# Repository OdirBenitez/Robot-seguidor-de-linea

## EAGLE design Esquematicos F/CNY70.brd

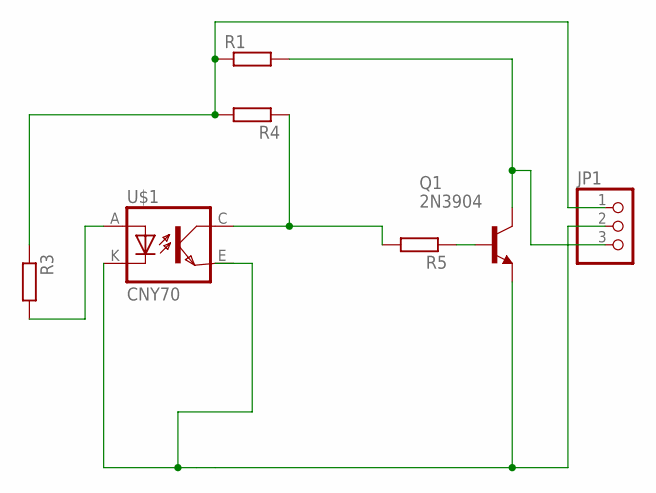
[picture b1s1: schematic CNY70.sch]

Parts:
JP1: PINHD-1X3; 1X03
Q1: 2N3904; TO92
R1, R3, R4, R5: R-EU_0207/10; 0207/10
U$1: CNY70; 4

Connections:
unnamed: Q1.2 (B), R5.1
unnamed: JP1.2, Q1.3 (E)
unnamed: JP1.1, R1.1, R3.1, R4.2
unnamed: U$1.E (EMI), U$1.K (C)
unnamed: JP1.3, Q1.1 (C), R1.2
unnamed: R3.2, U$1.A
unnamed: R4.1, R5.2, U$1.C (COL)

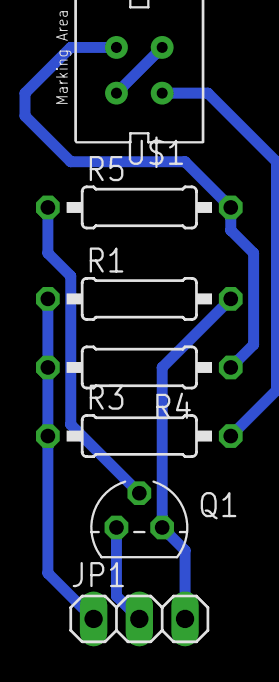
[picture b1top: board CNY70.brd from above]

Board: 2 copper layers, 7 parts (0 on the bottom side), 7 nets.

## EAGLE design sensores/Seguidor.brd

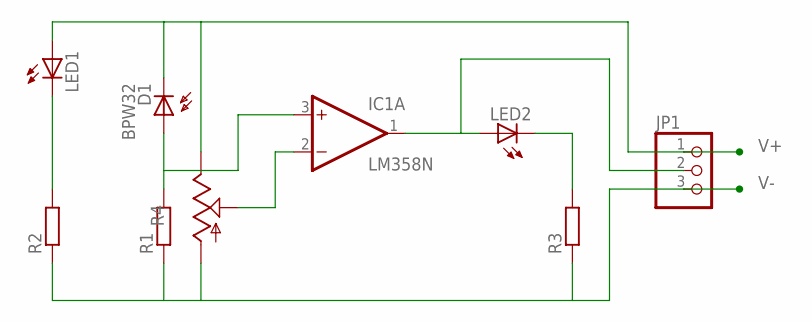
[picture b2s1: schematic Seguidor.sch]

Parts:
D1: BPW32
IC1: LM358N; DIL08
JP1: PINHD-1X3; 1X03
LED1, LED2: LED3MM
R1, R2, R3: R-EU_0207/12; 0207/12
R4: TRIM_US-B25P; B25P

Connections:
unnamed: D1.A, IC1.3 (+IN), R1.2
unnamed: LED1.K (C), R2.2
unnamed: IC1.1 (OUT), JP1.2, LED2.A
unnamed: IC1.2 (-IN), R4.S
unnamed: LED2.K (C), R3.2
V+: D1.K (C), IC1.8 (V+), JP1.1, LED1.A, R4.E
V-: IC1.4 (V-), JP1.3, R1.1, R2.1, R3.1, R4.A

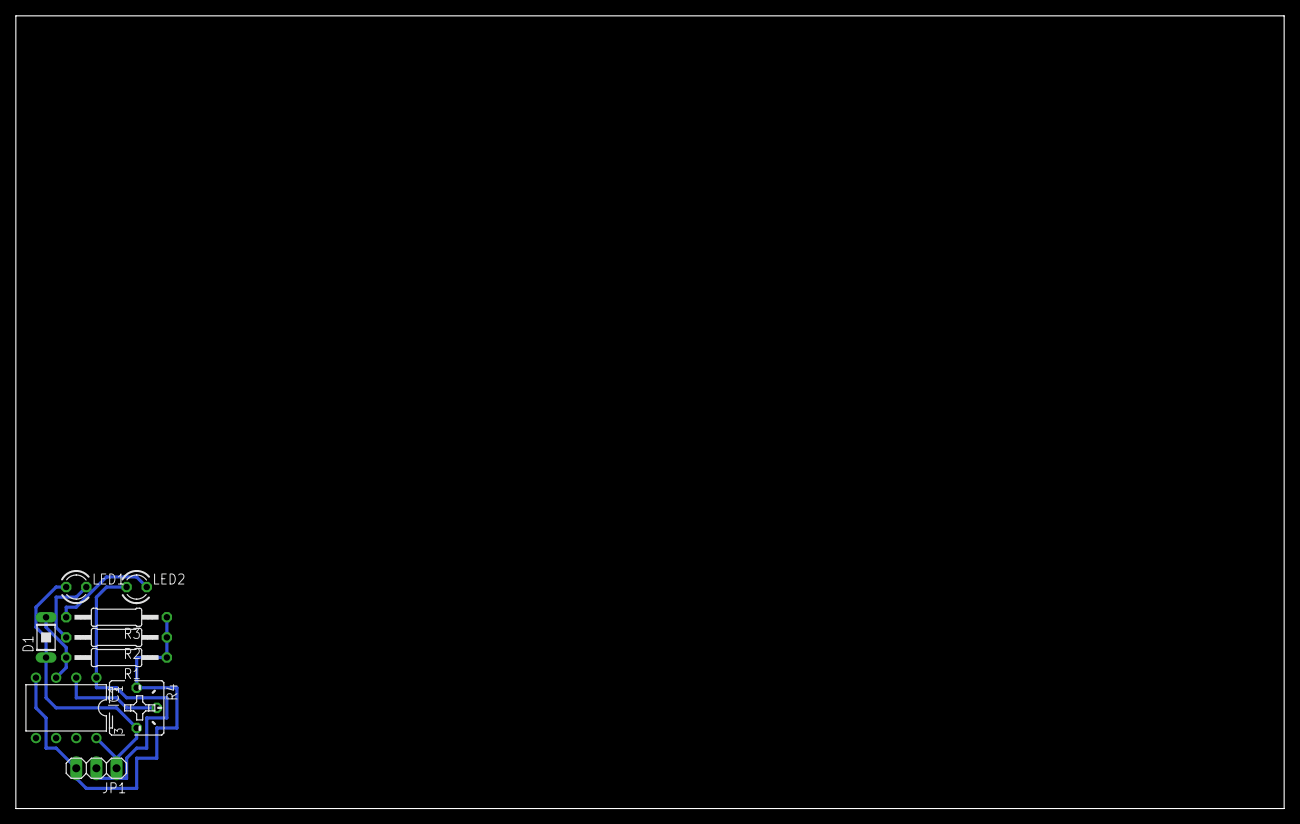
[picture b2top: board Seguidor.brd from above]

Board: 2 copper layers, 160.0 x 100.0 mm, 9 parts (0 on the bottom side), 7 nets.

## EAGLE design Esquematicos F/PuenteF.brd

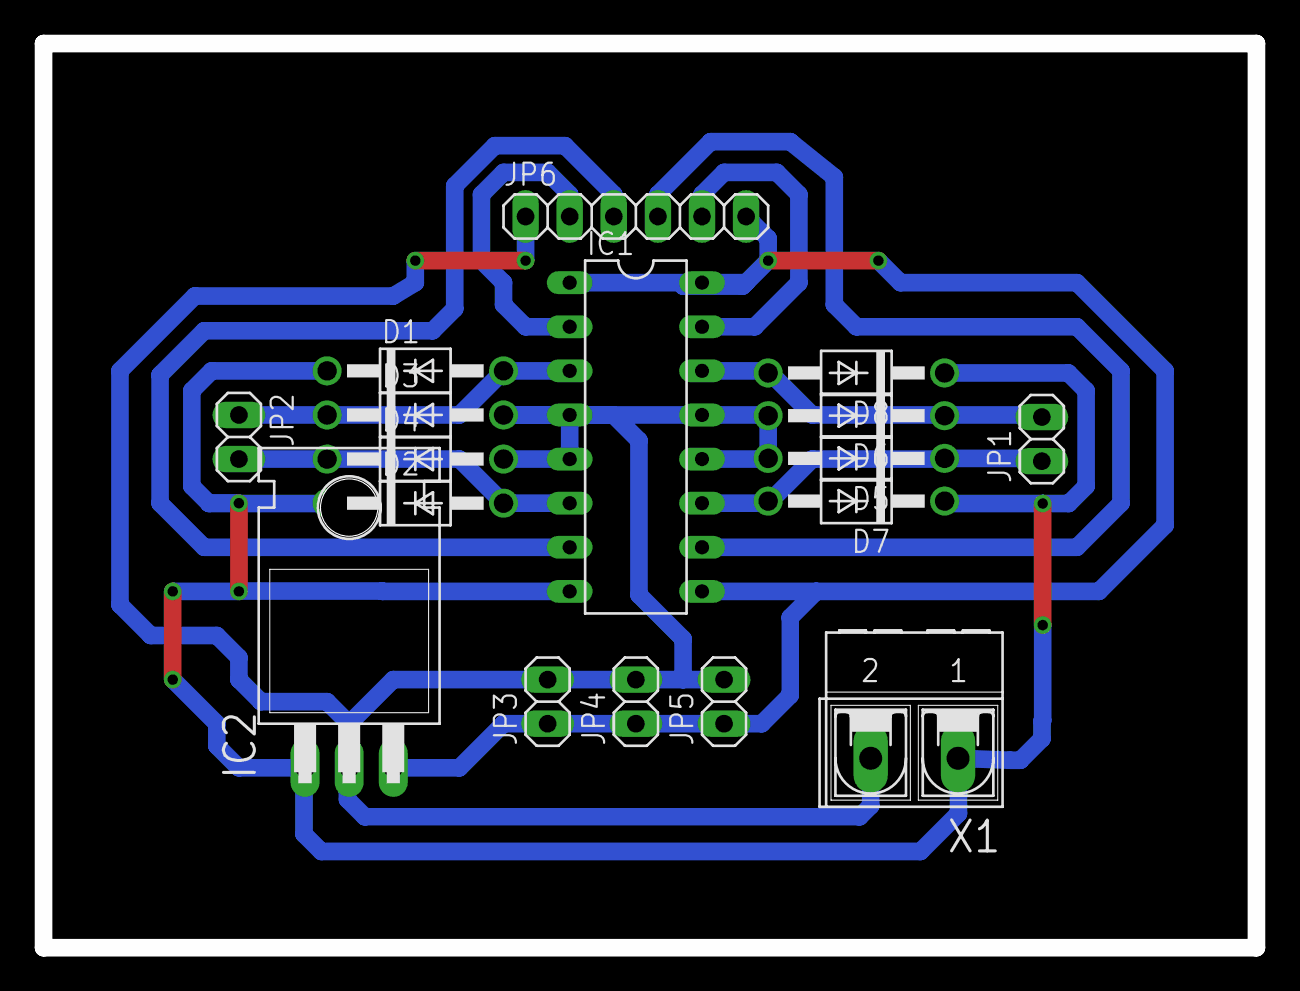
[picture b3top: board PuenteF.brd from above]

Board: 2 copper layers, 69.8 x 52.1 mm, 17 parts (0 on the bottom side), 11 nets.

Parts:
D1, D2, D3, D4, D5, D6, D7, D8: 1N4004; DO41-10
IC1: L293D; DIL16
IC2: 7805T; TO220H
JP1, JP2, JP3, JP4, JP5: 1X02
JP6: 1X06
X1: AK500/2-H

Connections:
+5V: IC1.1, IC1.9, IC1.16, IC2.3, JP3.1, JP4.1, JP5.1, JP6.6
+9V: D1.C, D2.C, D7.C, D8.C, IC1.8, IC2.1, X1.1
A: IC1.2, JP6.2
B: IC1.7, JP6.3
C: IC1.10, JP6.4
D: IC1.15, JP6.5
GND: D3.A, D4.A, D5.A, D6.A, IC1.4, IC1.5, IC1.12, IC1.13, IC2.2, JP3.2, JP4.2, JP5.2, JP6.1, X1.2
MOTOR1: D1.A, D3.C, IC1.3, JP2.1
MOTOR2: D2.A, D4.C, IC1.6, JP2.2
MOTOR3: D5.C, D7.A, IC1.11, JP1.1
MOTOR4: D6.C, D8.A, IC1.14, JP1.2

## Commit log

2018-05-19 Seguidor de Linea
    Documentacion
2018-06-12 Seguidor de linea
2018-06-12 Revert "Seguidor de linea"
    This reverts commit 7e3ef87126c8e1853c30779bc3a873d18d92e5d1.
2018-06-12 Programacion robot
2018-06-12 Programacion
2018-06-12 Sensores finales
2018-06-13 PuenteH
